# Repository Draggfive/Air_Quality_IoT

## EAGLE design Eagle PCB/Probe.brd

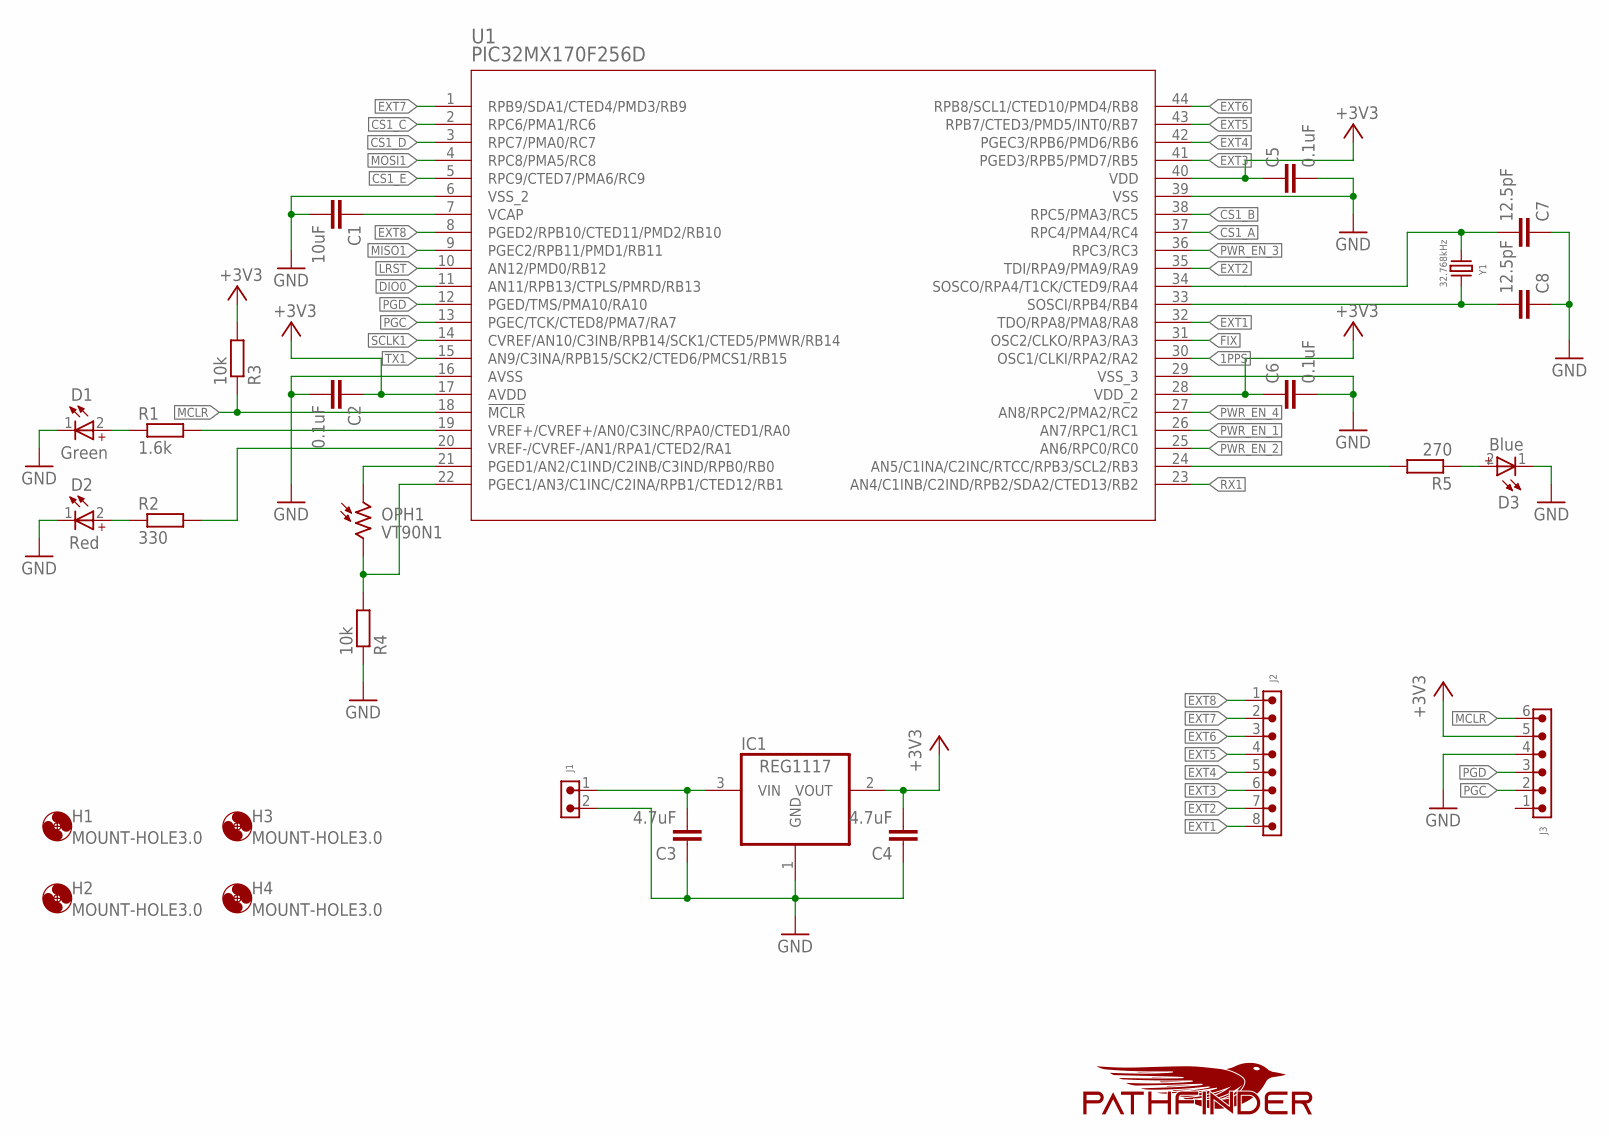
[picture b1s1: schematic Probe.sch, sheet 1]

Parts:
C1: 10uF; C0603
C2, C5, C6: 0.1uF; C0402
C3, C4: 4.7uF; C0805
C7, C8: 12.5pF; C0201
D1: Green; WL-SMCD_0603
D2: Red; WL-SMCD_0603
D3: Blue; WL-SMCD_0603
H1, H2, H3, H4: MOUNT-HOLE3.0; 3,0
IC1: REG1117; SOT223
J1: 6130XX11021_61300211021; 61300211021
J2: 6130XX11021_61300811021; 61300811021
J3: 6130XX11021_61300611021; 61300611021
OPH1: VT90N1; VT900
R1: 1.6k; R0402
R2: 330; R0402
R3, R4: 10k; R0402
R5: 270; R0402
U1: PIC32MX170F256D; TQFP44_10X10MC
U$1: PATHFINDER_LOGO24MM_6MIL_S; PATHFINDER_LOGO_24MM_6MIL_SERIGRAPHY
Y1: 32.768kHz; WE-XTAL_CFPX-217

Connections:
1PPS: U1.30 (OSC1/CLKI/RPA2/RA2); also elsewhere on the board
+3V3: C2.1, C4.2, C5.1, C6.1, IC1.2 (VOUT), J3.5, R3.2, U1.17 (AVDD), U1.28 (VDD_2), U1.40 (VDD); also elsewhere on the board
CS1_A: U1.37 (RPC4/PMA4/RC4); also elsewhere on the board
CS1_B: U1.38 (RPC5/PMA3/RC5); also elsewhere on the board
CS1_C: U1.2 (RPC6/PMA1/RC6); also elsewhere on the board
CS1_D: U1.3 (RPC7/PMA0/RC7); also elsewhere on the board
CS1_E: U1.5 (RPC9/CTED7/PMA6/RC9); also elsewhere on the board
DIO0: U1.11 (AN11/RPB13/CTPLS/PMRD/RB13); also elsewhere on the board
EXT1: J2.8, U1.32 (TDO/RPA8/PMA8/RA8)
EXT2: J2.7, U1.35 (TDI/RPA9/PMA9/RA9)
EXT3: J2.6, U1.41 (PGED3/RPB5/PMD7/RB5)
EXT4: J2.5, U1.42 (PGEC3/RPB6/PMD6/RB6)
EXT5: J2.4, U1.43 (RPB7/CTED3/PMD5/INT0/RB7)
EXT6: J2.3, U1.44 (RPB8/SCL1/CTED10/PMD4/RB8)
EXT7: J2.2, U1.1 (RPB9/SDA1/CTED4/PMD3/RB9)
EXT8: J2.1, U1.8 (PGED2/RPB10/CTED11/PMD2/RB10)
FIX: U1.31 (OSC2/CLKO/RPA3/RA3); also elsewhere on the board
GND: C1.2, C2.2, C3.1, C4.1, C5.2, C6.2, C7.1, C8.1, D1.1 (_), D2.1 (_), D3.1 (_), IC1.1 (GND), J1.2, J3.4, R4.1, U1.6 (VSS_2), U1.16 (AVSS), U1.29 (VSS_3), U1.39 (VSS); also elsewhere on the board
LRST: U1.10 (AN12/PMD0/RB12); also elsewhere on the board
MCLR: J3.6, R3.1, U1.18 (!MCLR)
MISO1: U1.9 (PGEC2/RPB11/PMD1/RB11); also elsewhere on the board
MOSI1: U1.4 (RPC8/PMA5/RC8); also elsewhere on the board
unnamed: C1.1, U1.7 (VCAP)
unnamed: C7.2, U1.34 (SOSCO/RPA4/T1CK/CTED9/RA4), Y1.2
unnamed: C8.2, U1.33 (SOSCI/RPB4/RB4), Y1.1
unnamed: D1.2 (+), R1.1
unnamed: D2.2 (+), R2.1
unnamed: OPH1.1, U1.21 (PGED1/AN2/C1IND/C2INB/C3IND/RPB0/RB0)
unnamed: R1.2, U1.19 (VREF+/CVREF+/AN0/C3INC/RPA0/CTED1/RA0)
unnamed: R2.2, U1.20 (VREF-/CVREF-/AN1/RPA1/CTED2/RA1)
unnamed: OPH1.2, R4.2, U1.22 (PGEC1/AN3/C1INC/C2INA/RPB1/CTED12/RB1)
unnamed: C3.2, IC1.3 (VIN), J1.1
unnamed: R5.2, U1.24 (AN5/C1INA/C2INC/RTCC/RPB3/SCL2/RB3)
unnamed: D3.2 (+), R5.1
PGC: J3.2, U1.13 (PGEC/TCK/CTED8/PMA7/RA7)
PGD: J3.3, U1.12 (PGED/TMS/PMA10/RA10)
PWR_EN_1: U1.26 (AN7/RPC1/RC1); also elsewhere on the board
PWR_EN_2: U1.25 (AN6/RPC0/RC0); also elsewhere on the board
PWR_EN_3: U1.36 (RPC3/RC3); also elsewhere on the board
PWR_EN_4: U1.27 (AN8/RPC2/PMA2/RC2); also elsewhere on the board
RX1: U1.23 (AN4/C1INB/C2IND/RPB2/SDA2/CTED13/RB2); also elsewhere on the board
SCLK1: U1.14 (CVREF/AN10/C3INB/RPB14/SCK1/CTED5/PMWR/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); also elsewhere on the board
TX1: U1.15 (AN9/C3INA/RPB15/SCK2/CTED6/PMCS1/RB15); also elsewhere on the board

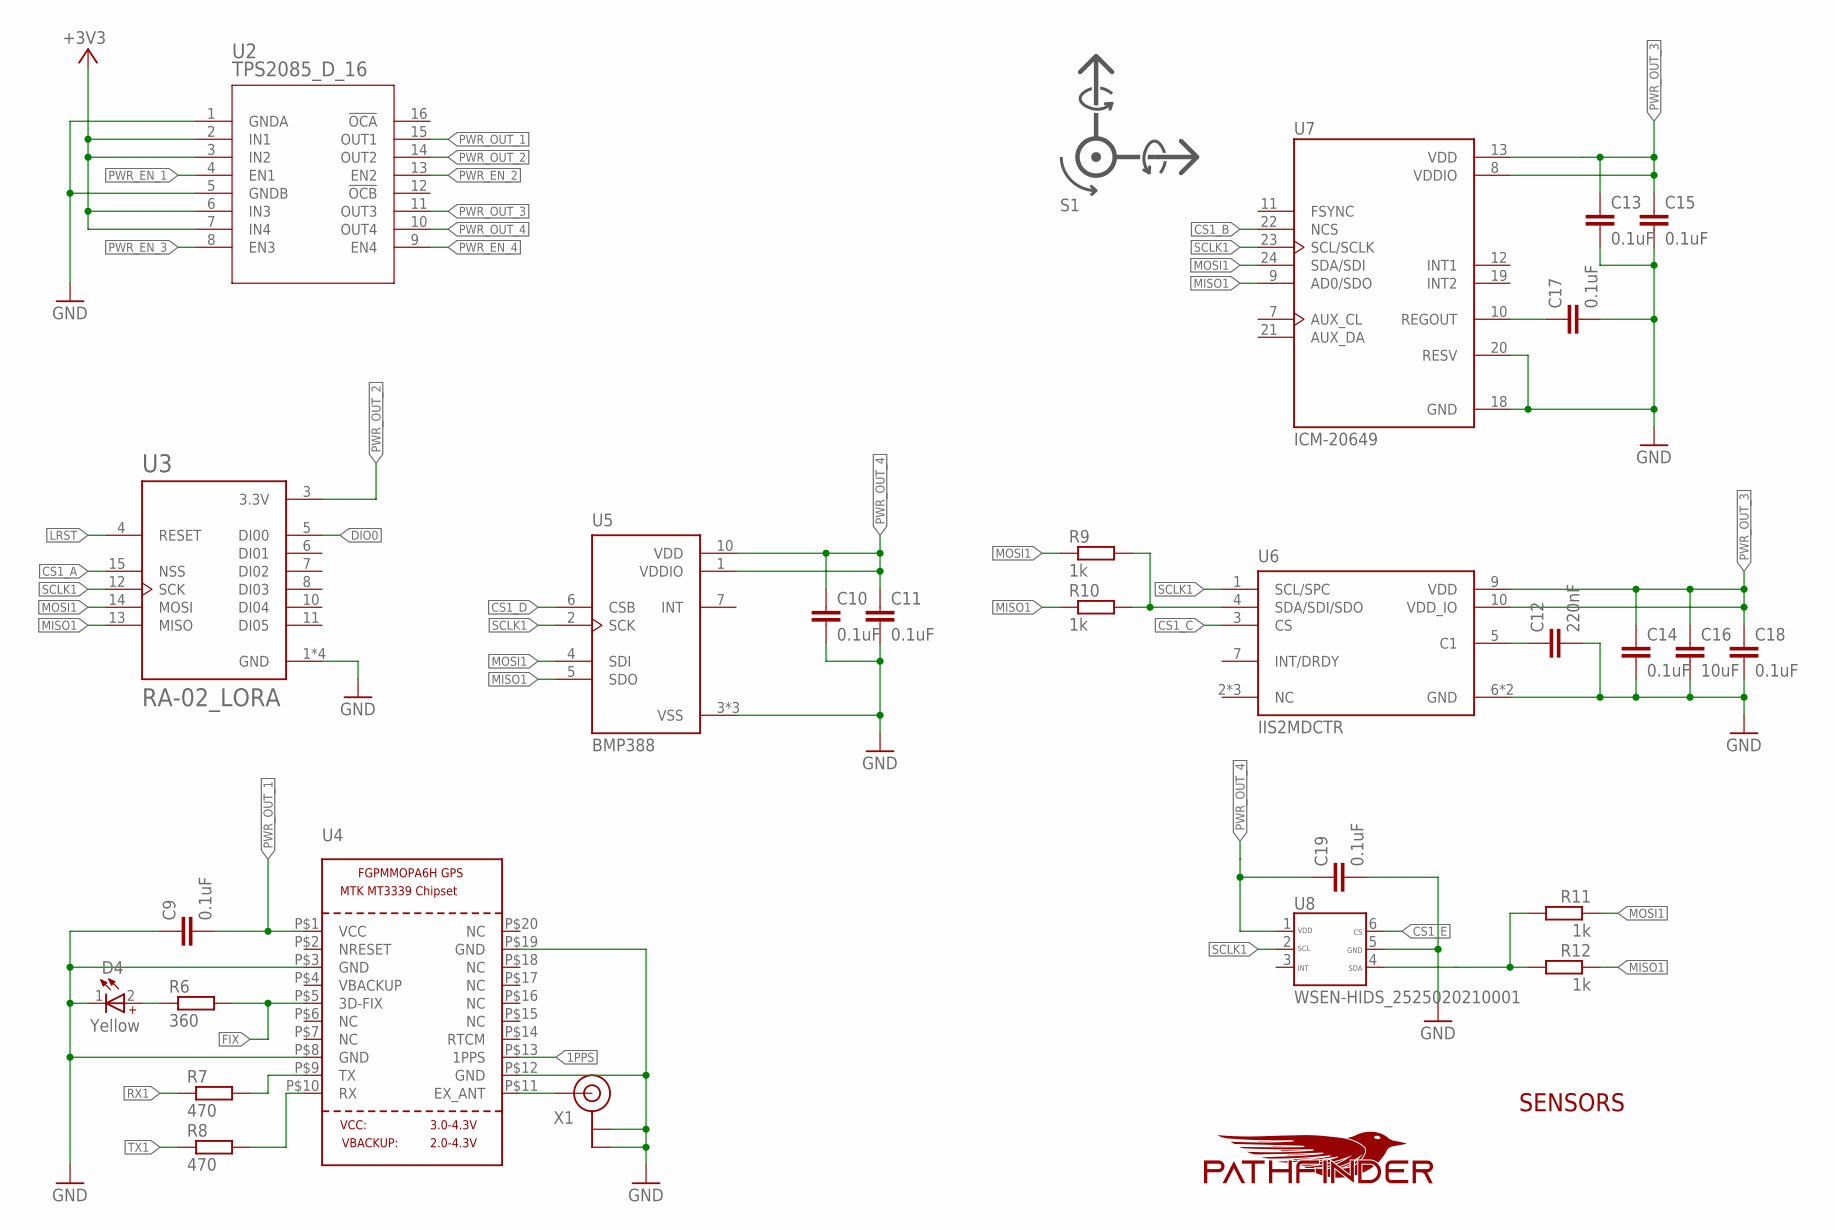
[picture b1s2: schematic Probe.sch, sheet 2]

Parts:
C9, C10, C11, C13, C14, C15, C17, C18, C19: 0.1uF; C0402
C12: 220nF; C0402
C16: 10uF; C0603
D4: Yellow; WL-SMCD_0603
R6: 360; R0402
R7, R8: 470; R0402
R9, R10, R11, R12: 1k; R0402
S1: COORDINATE_SYSTEM; DIRECT_AXES
U2: TPS2085_D_16; D16
U3: RA-02_LORA; MODULE_RA-02_LORA
U4: GPS_FGPMMOPA6H; FGPMMOPA6H
U5: BMP388; PQFN50P200X200X80-10N
U6: IIS2MDCTR; LGA12R50P4X4_200X200X70
U7: ICM-20649; QFN40P300X300X95-24N
U8: WSEN-HIDS_2525020210001; WSEN-HIDS_2525020210001_SIMPLE
U$2: PATHFINDER_LOGO24MM_6MIL_S; PATHFINDER_LOGO_24MM_6MIL_SERIGRAPHY
X1: ANTENNA_U.FL; U.FL

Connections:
1PPS: U4.P$13 (1PPS); also elsewhere on the board
+3V3: U2.2 (IN1), U2.3 (IN2), U2.6 (IN3), U2.7 (IN4); also elsewhere on the board
CS1_A: U3.15 (NSS); also elsewhere on the board
CS1_B: U7.22 (NCS); also elsewhere on the board
CS1_C: U6.3 (CS); also elsewhere on the board
CS1_D: U5.6 (CSB); also elsewhere on the board
CS1_E: U8.6 (CS); also elsewhere on the board
DIO0: U3.5 (DI00); also elsewhere on the board
FIX: R6.2, U4.P$5 (3D-FIX); also elsewhere on the board
GND: C9.1, C10.2, C11.2, C12.2, C13.2, C14.2, C15.2, C16.2, C17.2, C18.2, C19.2, D4.1 (_), U2.1 (GNDA), U2.5 (GNDB), U3.1 (GND), U3.2 (GND), U3.9 (GND), U3.16 (GND), U4.P$3 (GND), U4.P$8 (GND), U4.P$12 (GND), U4.P$19 (GND), U5.3 (VSS), U5.8 (VSS), U5.9 (VSS), U6.6 (GND), U6.8 (GND), U7.18 (GND), U7.20 (RESV), U8.5 (GND), X1.1 (GND), X1.2 (GND); also elsewhere on the board
LRST: U3.4 (RESET); also elsewhere on the board
MISO1: R10.1, R12.1, U3.13 (MISO), U5.5 (SDO), U7.9 (AD0/SDO); also elsewhere on the board
MOSI1: R9.1, R11.1, U3.14 (MOSI), U5.4 (SDI), U7.24 (SDA/SDI); also elsewhere on the board
unnamed: C17.1, U7.10 (REGOUT)
unnamed: D4.2 (+), R6.1
unnamed: U4.P$11 (EX_ANT), X1.3 (SIGNAL)
unnamed: R7.2, U4.P$9 (TX)
unnamed: R8.2, U4.P$10 (RX)
unnamed: R9.2, R10.2, U6.4 (SDA/SDI/SDO)
unnamed: C12.1, U6.5 (C1)
unnamed: R11.2, R12.2, U8.4 (SDA)
PWR_EN_1: U2.4 (EN1); also elsewhere on the board
PWR_EN_2: U2.13 (EN2); also elsewhere on the board
PWR_EN_3: U2.8 (EN3); also elsewhere on the board
PWR_EN_4: U2.9 (EN4); also elsewhere on the board
PWR_OUT_1: C9.2, U2.15 (OUT1), U4.P$1 (VCC)
PWR_OUT_2: U2.14 (OUT2), U3.3 (3.3V)
PWR_OUT_3: C13.1, C14.1, C15.1, C16.1, C18.1, U2.11 (OUT3), U6.9 (VDD), U6.10 (VDD_IO), U7.8 (VDDIO), U7.13 (VDD)
PWR_OUT_4: C10.1, C11.1, C19.1, U2.10 (OUT4), U5.1 (VDDIO), U5.10 (VDD), U8.1 (VDD)
RX1: R7.1; also elsewhere on the board
SCLK1: U3.12 (SCK), U5.2 (SCK), U6.1 (SCL/SPC), U7.23 (SCL/SCLK), U8.2 (SCL); also elsewhere on the board
TX1: R8.1; also elsewhere on the board

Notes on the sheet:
SENSORS

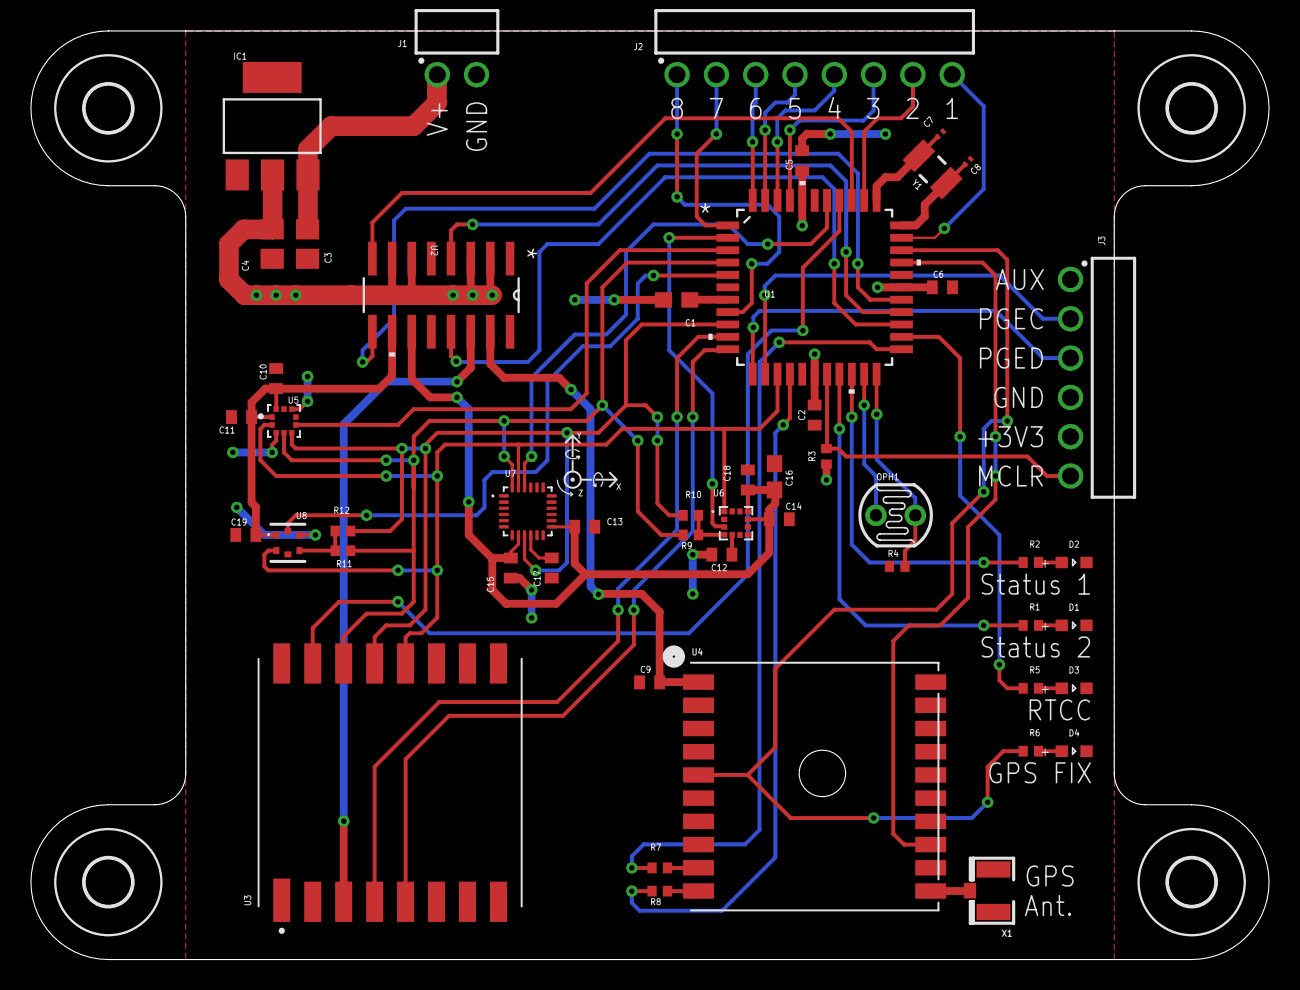
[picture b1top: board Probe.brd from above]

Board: 2 copper layers, 80.0 x 60.0 mm, 57 parts (1 on the bottom side), 55 nets.

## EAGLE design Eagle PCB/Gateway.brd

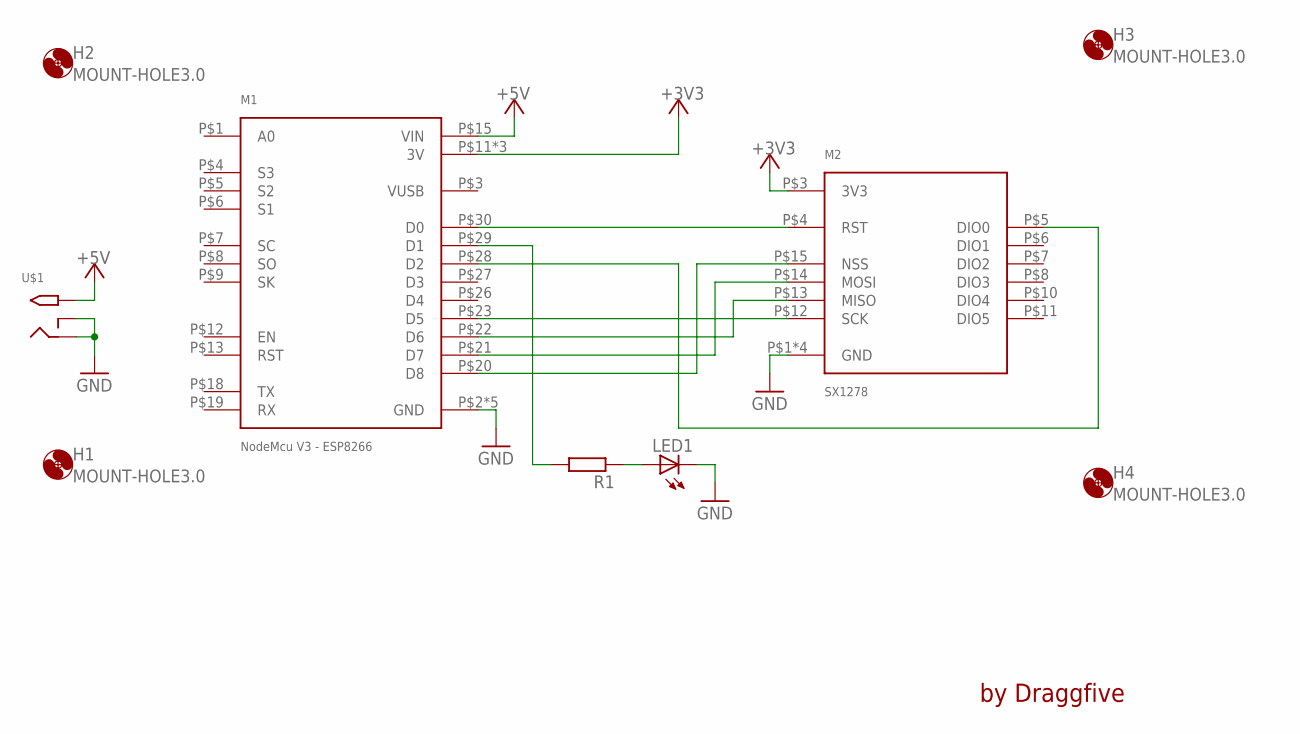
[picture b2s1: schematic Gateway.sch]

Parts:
H1, H2, H3, H4: MOUNT-HOLE3.0; 3,0
LED1: LED5MM
M1: NodeMcu V3 - ESP8266; NODEMCU_V3
M2: SX1278
R1: R-EU_0207/10; 0207/10
U$1: 2.1MMJACKTHM; PJ-102A

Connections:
+3V3: M1.P$11 (3V), M1.P$16 (3V), M1.P$25 (3V), M2.P$3 (3V3)
+5V: M1.P$15 (VIN), U$1.TIP
GND: LED1.K (C), M1.P$2 (GND), M1.P$10 (GND), M1.P$14 (GND), M1.P$17 (GND), M1.P$24 (GND), M2.P$1 (GND), M2.P$2 (GND), M2.P$9 (GND), M2.P$16 (GND), U$1.RING, U$1.RING_SW
unnamed: M1.P$29 (D1), R1.2
unnamed: M1.P$30 (D0), M2.P$4 (RST)
unnamed: M1.P$28 (D2), M2.P$5 (DIO0)
unnamed: M1.P$23 (D5), M2.P$12 (SCK)
unnamed: M1.P$22 (D6), M2.P$13 (MISO)
unnamed: M1.P$21 (D7), M2.P$14 (MOSI)
unnamed: M1.P$20 (D8), M2.P$15 (NSS)
unnamed: LED1.A, R1.1

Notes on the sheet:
by Draggfive

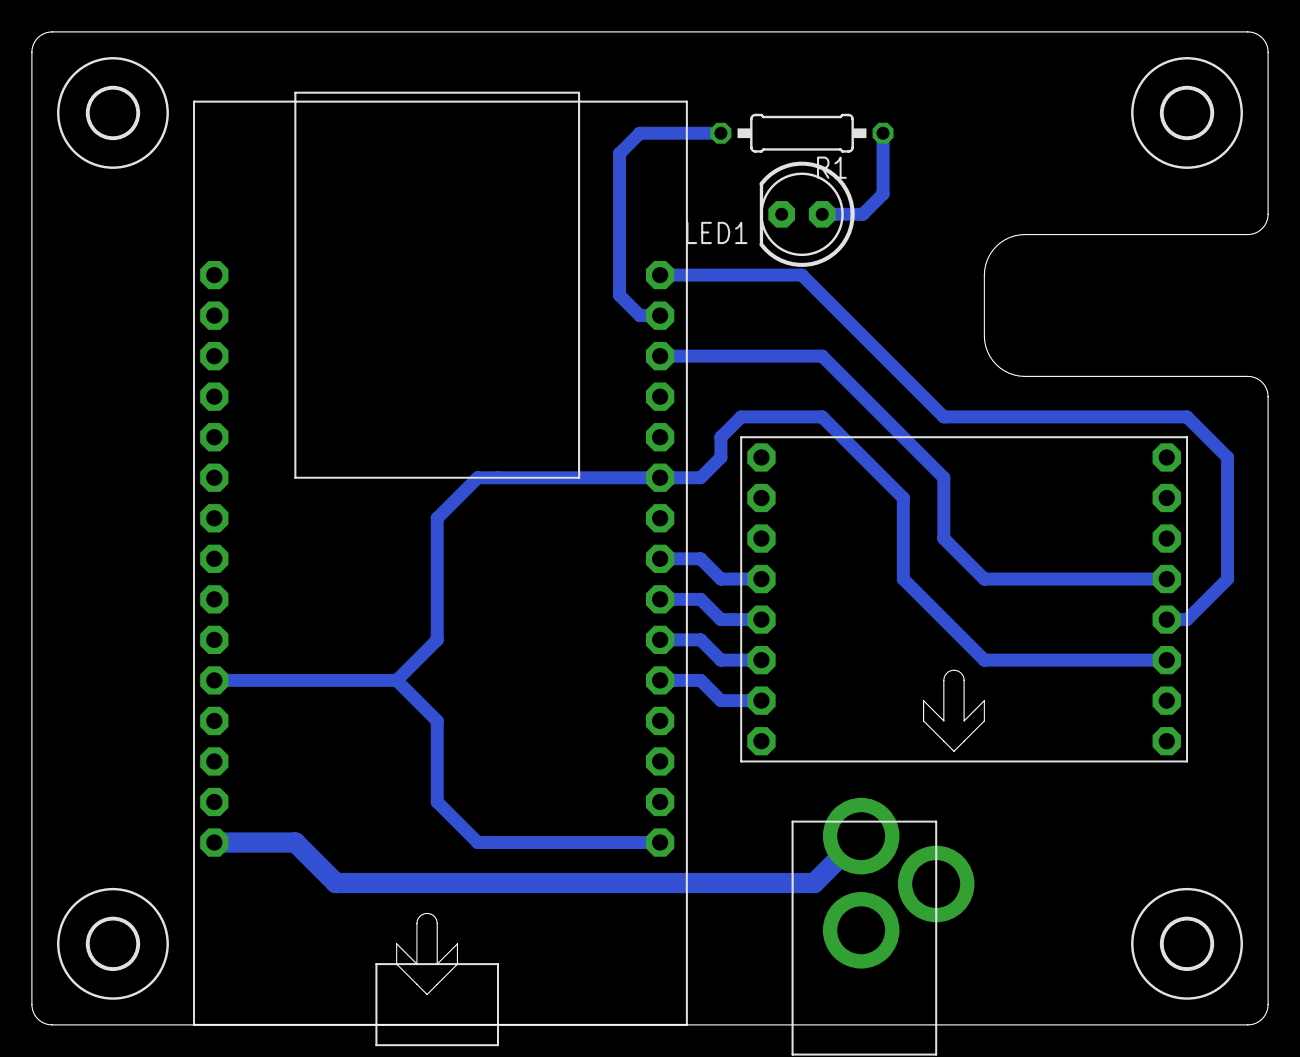
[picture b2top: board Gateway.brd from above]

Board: 2 copper layers, 77.5 x 62.2 mm, 9 parts (0 on the bottom side), 11 nets.

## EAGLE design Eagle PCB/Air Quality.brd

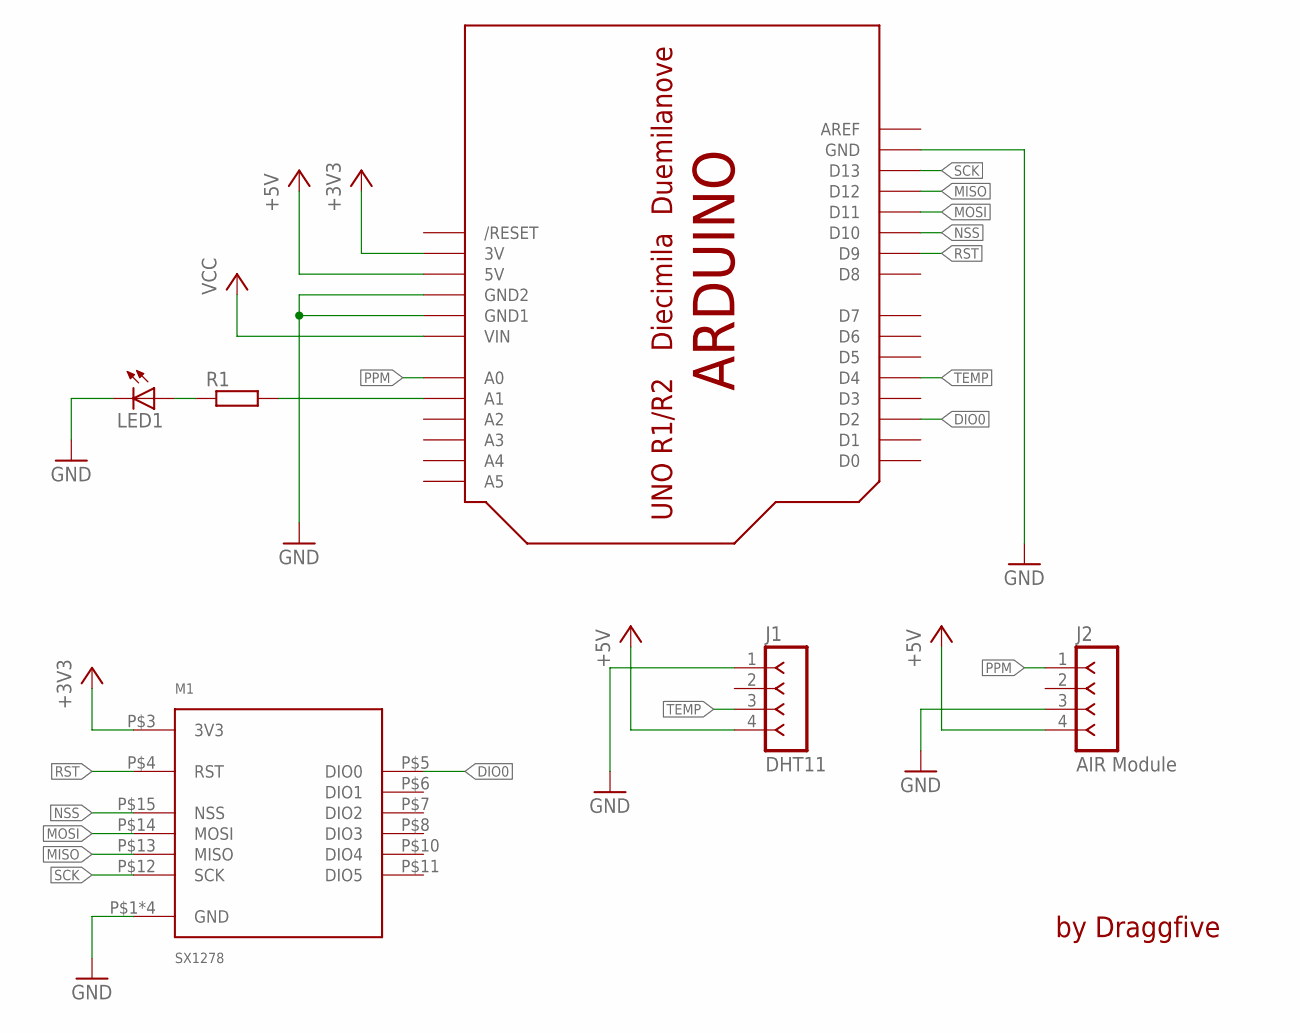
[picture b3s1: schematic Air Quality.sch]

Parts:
J1: DHT11; SIP-100-04-32Y
J2: AIR Module; SIP-100-04-40Y
LED1: LED5MM
M1: SX1278
R1: R-EU_0207/10; 0207/10
U$1: ARDUINOUNO; ARDUINO

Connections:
+3V3: M1.P$3 (3V3), U$1.3V
+5V: J1.4, J2.4, U$1.5V
DIO0: M1.P$5 (DIO0), U$1.D2
GND: J1.1, J2.3, LED1.K (C), M1.P$1 (GND), M1.P$2 (GND), M1.P$9 (GND), M1.P$16 (GND), U$1.GND, U$1.GND1, U$1.GND2
MISO: M1.P$13 (MISO), U$1.D12
MOSI: M1.P$14 (MOSI), U$1.D11
unnamed: LED1.A, R1.1
unnamed: R1.2, U$1.A1
NSS: M1.P$15 (NSS), U$1.D10
PPM: J2.1, U$1.A0
RST: M1.P$4 (RST), U$1.D9
SCK: M1.P$12 (SCK), U$1.D13
TEMP: J1.3, U$1.D4
VCC: U$1.VIN

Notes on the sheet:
by Draggfive

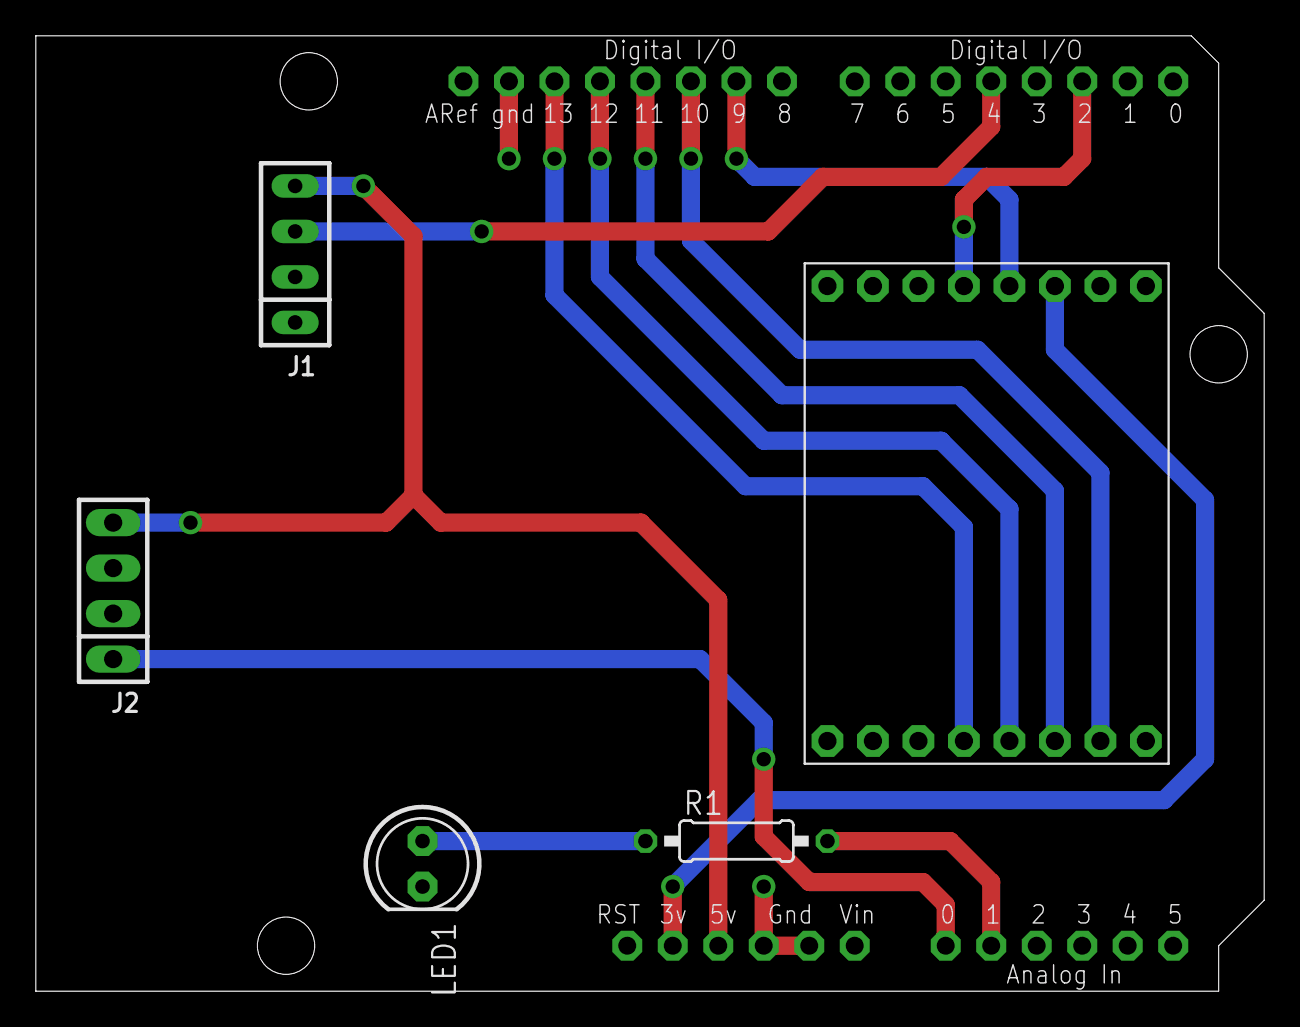
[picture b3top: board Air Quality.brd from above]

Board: 2 copper layers, 68.6 x 53.3 mm, 6 parts (0 on the bottom side), 13 nets.

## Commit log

2021-03-29 Assignment Update
2021-03-29 Removed Local Credentials
2021-03-29 Work in Progress
2021-04-22 Added support for industrial manufacturing

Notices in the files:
parts and their libraries:
con-headers-jp: Copyright (C) 2008, Bob Starr
Wurth_LEDs_WL-SMCD: Copyright: Würth Elektronik
